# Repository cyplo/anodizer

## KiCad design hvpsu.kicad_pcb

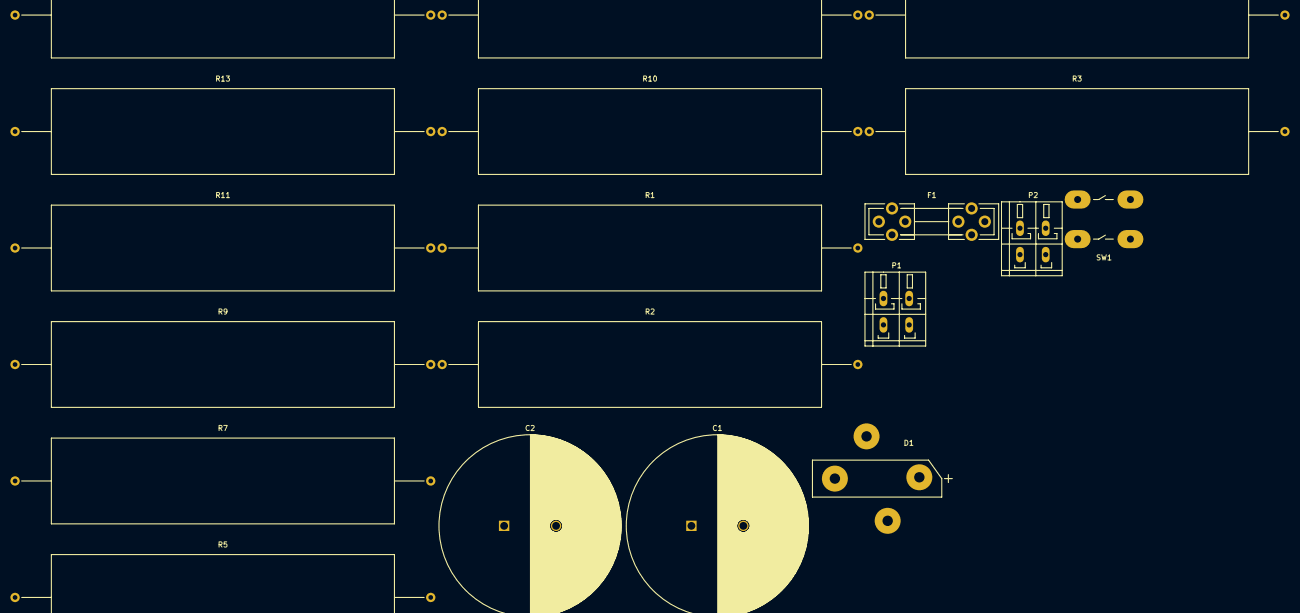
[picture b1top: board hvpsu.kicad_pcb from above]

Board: 2 copper layers, 19 parts (0 on the bottom side), 14 nets, no tracks yet.

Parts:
C1, C2: 680uF; C_Radial_D35_L51_P10
D1: KBU10M; KBU10M_Bridge_Rectifier_1000V
F1: FUSE; Fuseholder5x20_horiz_open_universal_Type-III
P1, P2: CONN_01X02; TerminalBlock_WAGO-236_2Stift_RM5mm_2pol
R1, R2, R3, R4, R5, R9, R10, R11, R12, R13: 1k; Resistor_Ceramic_Horizontal_L65mm-W16mm-H15mm-p80mm
R6, R7: 0R; Resistor_Ceramic_Horizontal_L65mm-W16mm-H15mm-p80mm
SW1: Switch_DPST; DPST_Rocker_Switch_Chily_3024_Angled

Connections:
GND: C1.2, C2.2, P2.2, R1.2
unnamed: C1.1, C2.1, P2.1, R6.1, R13.1
unnamed: F1.1, SW1.4
unnamed: P1.1, SW1.1
unnamed: P1.2, SW1.3
unnamed: R1.1, R2.1
unnamed: R2.2, R3.2
unnamed: R3.1, R4.1
unnamed: R4.2, R5.2
unnamed: R6.2, R7.2
unnamed: R9.1, R10.1
unnamed: R5.1, R10.2
unnamed: R11.1, R12.1
unnamed: R12.2, R13.2

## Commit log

2015-06-07 emptied readme, to make space for more
2015-06-07 basic version of the HV part
2015-06-07 fitlering cap and annotations
2015-06-09 DPST switch's footprint added
2015-06-09 most footprints added
2015-06-16 all footprints added
2015-06-16 duplicated footprint removed
2015-06-16 autospread all components on the pcb
